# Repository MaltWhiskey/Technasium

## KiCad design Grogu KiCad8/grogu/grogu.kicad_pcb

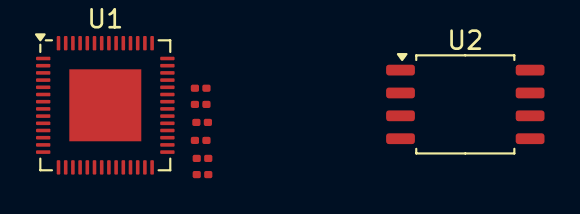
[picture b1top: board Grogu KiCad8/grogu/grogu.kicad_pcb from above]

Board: 2 copper layers, 8 parts (0 on the bottom side), 14 nets, no tracks yet.

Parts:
R1, R2, R3, R4, R5, R6: 0; R_0201_0603Metric
U1: ESP32-S3; QFN-56-1EP_7x7mm_P0.4mm_EP4x4mm
U2: W25Q128JVS; SOIC-8_5.23x5.23mm_P1.27mm

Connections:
/SPICLK: R4.2, U2.6 (CLK)
/SPICS: R3.2, U2.1 (~CS)
/SPID: R6.2, U2.5 (DI(IO0))
/SPIHD: R1.2, U2.7 (IO3)
/SPIQ: R5.2, U2.2 (DO(IO1))
/SPIWD: R2.2, U2.3 (IO2)
GND: U1.57 (GND), U2.8 (VCC)
unnamed: R4.1, U1.33 (SPICLK)
unnamed: R3.1, U1.32 (SPICS0)
unnamed: R6.1, U1.35 (SPID)
unnamed: R1.1, U1.30 (SPIHD)
unnamed: R5.1, U1.34 (SPIQ)
unnamed: R2.1, U1.31 (SPIWP)
VCC: U1.2 (VDD3P3), U1.3 (VDD3P3), U1.20 (VDD3P3_RTC), U1.29 (VDD_SPI), U1.46 (VDD3P3_CPU), U1.55 (VDDA), U1.56 (VDDA), U2.4 (GND)

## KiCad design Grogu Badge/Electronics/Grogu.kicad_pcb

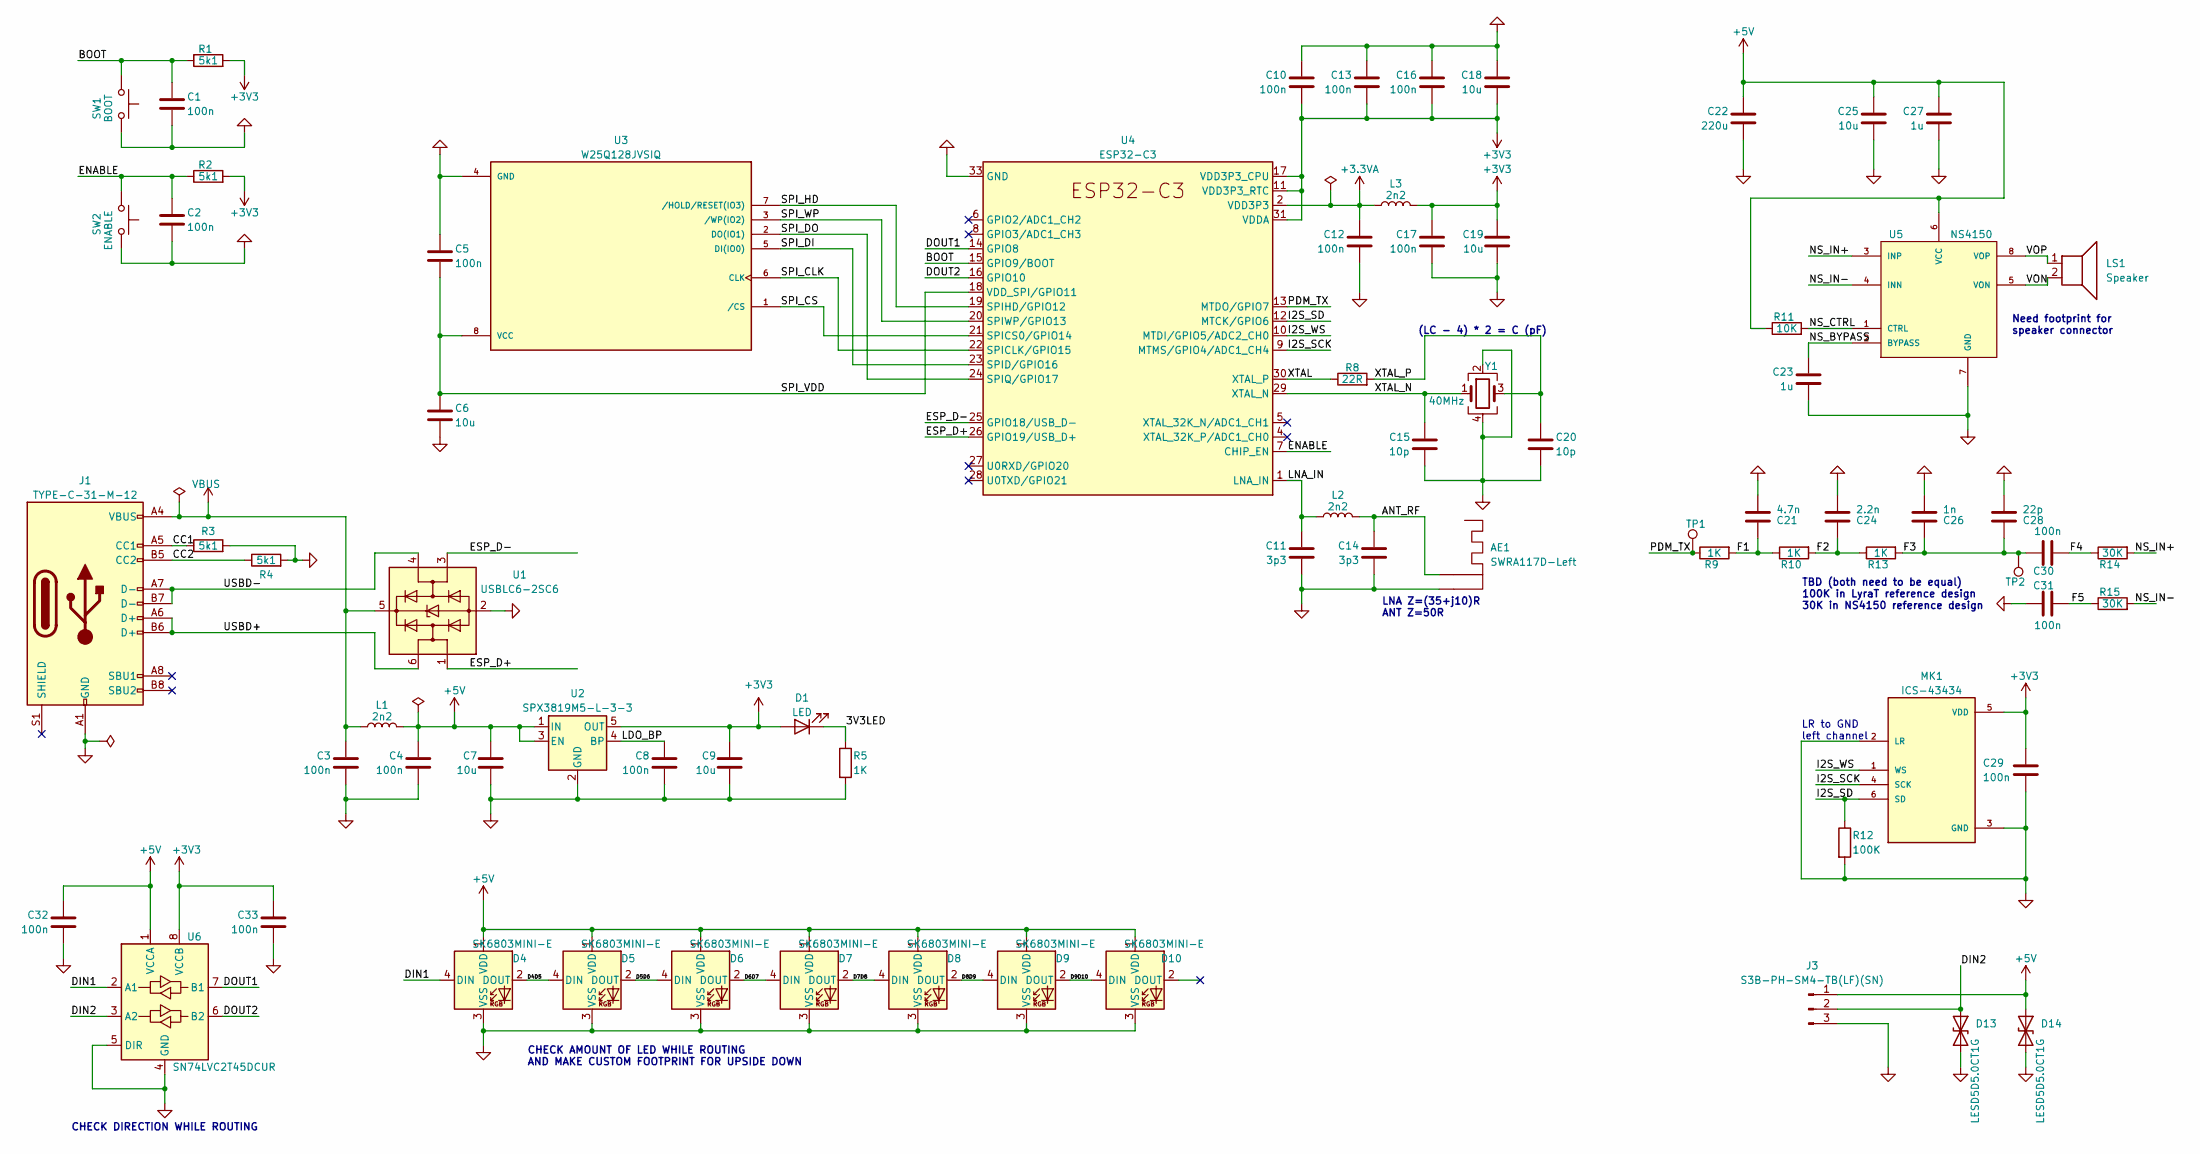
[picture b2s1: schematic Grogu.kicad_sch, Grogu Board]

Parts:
AE1: SWRA117D-Left; SWRA117D_2.4GHz_Left; PART# SWRA117D
C1, C2, C3, C4, C5, C8, C10, C12, C13, C16, C17, C29, C30, C31, C32, C33: 100n; C_0402_1005Metric; PART# C1525
C6, C7, C9, C18, C19, C25: 10u; C_0603_1608Metric; PART# C19702
C11, C14: 3p3; C_0402_1005Metric; PART# C1565
C15, C20: 10p; C_0402_1005Metric; PART# C32949
C21: 4.7n; C_0402_1005Metric; PART# C1538
C22: 220u; CP_Elec_6.3x7.7; PART# C340768
C23, C27: 1u; C_0805_2012Metric; PART# C15849
C24: 2.2n; C_0402_1005Metric; PART# C106861
C26: 1n; C_0402_1005Metric; PART# C106205
C28: 22p; C_0402_1005Metric; PART# C106203
D1: LED; LED_0805_2012Metric; PART# C84260
D4, D5, D6, D7, D8, D9, D10: SK6803MINI-E; LED_SK6812MINI_PLCC4_3.5x3.5mm_P1.75mm; PART# SK6803MINI-E
D13, D14: LESD5D5.0CT1G; D_SOD-523; PART# C383211
J1: TYPE-C-31-M-12; USB_C_Receptacle_HRO_TYPE-C-31-M-12; PART# C165948
J3: S3B-PH-SM4-TB(LF)(SN); JST_PH_S3B-PH-SM4-TB_1x03-1MP_P2.00mm_Horizontal; PART# C265101
L1, L2, L3: 2n2; L_0402_1005Metric; PART# C412264
LS1: Speaker; Speaker-0.5W-8Ohm
MK1: ICS-43434; PART# ICS-43434
R1, R2, R3, R4: 5k1; R_0402_1005Metric; PART# C105873
R5, R9, R10, R13: 1K; R_0402_1005Metric; PART# C25744
R8: 22R; R_0402_1005Metric; PART# C25092
R11: 10K; R_0402_1005Metric; PART# C25744
R12: 100K; R_0402_1005Metric; PART# C11702
R14, R15: 30K; R_0402_1005Metric; PART# C25744
SW1: BOOT; TS-1187A-B-A-B; PART# C318884
SW2: ENABLE; TS-1187A-B-A-B; PART# C318884
TP1, TP2: TestPoint; TestPoint_Pad_1.5x1.5mm
U1: USBLC6-2SC6; SOT-23-6; PART# C7519
U2: SPX3819M5-L-3-3; SOT-23-5; PART# C9055
U3: W25Q128JVSIQ; SOIC-8_5.275x5.275mm_P1.27mm; PART# C97521
U4: ESP32-C3; QFN-32-1EP_5x5mm_P0.5mm_EP3.45x3.45mm; PART# C2838500
U5: NS4150; MSOP-8_3x3mm_P0.65mm; PART# C189961
U6: SN74LVC2T45DCUR; VSSOP-8_2.4x2.1mm_P0.5mm; PART# C15741
Y1: 40MHz; Crystal_SMD_2520-4Pin_2.5x2.0mm; PART# C255973

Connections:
+3.3VA: C12.1, L3.1, U4.2 (VDD3P3), U4.3 (VDD3P3)
+3V3: C9.1, C10.1, C13.1, C16.1, C17.1, C18.1, C19.1, C29.1, C33.1, D1.2 (A), L3.2, MK1.5 (VDD), R1.2, R2.2, U2.5 (OUT), U4.11 (VDD3P3_RTC), U4.17 (VDD3P3_CPU), U4.31 (VDDA), U4.32 (VDDA), U6.8 (VCCB)
+5V: C4.1, C7.1, C22.2, C25.2, C27.2, C32.1, D4.1 (VDD), D5.1 (VDD), D6.1 (VDD), D7.1 (VDD), D8.1 (VDD), D9.1 (VDD), D10.1 (VDD), D14.1 (A1), J3.1, L1.2, R11.1, U2.1 (IN), U2.3 (EN), U5.6 (VCC), U6.1 (VCCA); also elsewhere on the board
/3V3LED: D1.1 (K), R5.1
/ANT_RF: AE1.2 (Feed), C14.1, L2.2
/BOOT: C1.1, R1.1, SW1.1, U4.15 (GPIO9/BOOT)
/CC1: J1.A5 (CC1), R3.1
/CC2: J1.B5 (CC2), R4.1
/D4D5: D4.2 (DOUT), D5.4 (DIN)
/D5D6: D5.2 (DOUT), D6.4 (DIN)
/D6D7: D6.2 (DOUT), D7.4 (DIN)
/D7D8: D7.2 (DOUT), D8.4 (DIN)
/D8D9: D8.2 (DOUT), D9.4 (DIN)
/D9D10: D9.2 (DOUT), D10.4 (DIN)
/DIN1: D4.4 (DIN), U6.2 (A1)
/DIN2: D13.1 (A1), J3.2, U6.3 (A2)
/DOUT1: U4.14 (GPIO8), U6.7 (B1)
/DOUT2: U4.16 (GPIO10), U6.6 (B2)
/ENABLE: C2.1, R2.1, SW2.1, U4.7 (CHIP_EN)
/ESP_D+: U1.1 (I/O1), U4.26 (GPIO19/USB_D+)
/ESP_D-: U1.3 (I/O2), U4.25 (GPIO18/USB_D-)
/F1: C21.2, R9.2, R10.1
/F2: C24.2, R10.2, R13.1
/F3: C26.2, C28.2, C30.2, R13.2, TP2.1
/F4: C30.1, R14.1
/F5: C31.1, R15.1
/I2S_SCK: MK1.4 (SCK), U4.9 (MTMS/GPIO4/ADC1_CH4)
/I2S_SD: MK1.6 (SD), R12.1, U4.12 (MTCK/GPIO6)
/I2S_WS: MK1.1 (WS), U4.10 (MTDI/GPIO5/ADC2_CH0)
/LDO_BP: C8.1, U2.4 (BP)
/LNA_IN: C11.1, L2.1, U4.1 (LNA_IN)
/NS_BYPASS: C23.2, U5.2 (BYPASS)
/NS_CTRL: R11.2, U5.1 (CTRL)
/NS_IN+: R14.2, U5.3 (INP)
/NS_IN-: R15.2, U5.4 (INN)
/PDM_TX: R9.1, TP1.1, U4.13 (MTDO/GPIO7)
/SPI_CLK: U3.6 (CLK), U4.22 (SPICLK/GPIO15)
/SPI_CS: U3.1 (/CS), U4.21 (SPICS0/GPIO14)
/SPI_DI: U3.5 (DI(IO0)), U4.23 (SPID/GPIO16)
/SPI_DO: U3.2 (DO(IO1)), U4.24 (SPIQ/GPIO17)
/SPI_HD: U3.7 (/HOLD/RESET(IO3)), U4.19 (SPIHD/GPIO12)
/SPI_VDD: C5.2, C6.1, U3.8 (VCC), U4.18 (VDD_SPI/GPIO11)
/SPI_WP: U3.3 (/WP(IO2)), U4.20 (SPIWP/GPIO13)
/USBD+: J1.A6 (D+), J1.B6 (D+), U1.6 (I/O1)
/USBD-: J1.A7 (D-), J1.B7 (D-), U1.4 (I/O2)
/VON: LS1.2, U5.5 (VON)
/VOP: LS1.1, U5.8 (VOP)
/XTAL: R8.1, U4.30 (XTAL_P)
/XTAL_N: C15.1, U4.29 (XTAL_N), Y1.1
/XTAL_P: C20.1, R8.2, Y1.3
GND: AE1.1 (Via), C1.2, C2.2, C3.2, C4.2, C5.1, C6.2, C7.2, C8.2, C9.2, C10.2, C11.2, C12.2, C13.2, C14.2, C15.2, C16.2, C17.2, C18.2, C19.2, C20.2, C21.1, C22.1, C23.1, C24.1, C25.1, C26.1, C27.1, C28.1, C29.2, C31.2, C32.2, C33.2, D4.3 (VSS), D5.3 (VSS), D6.3 (VSS), D7.3 (VSS), D8.3 (VSS), D9.3 (VSS), D10.3 (VSS), D13.2 (A2), D14.2 (A2), J1.A1 (GND), J1.A12 (GND), J1.B1 (GND), J1.B12 (GND), J3.3, MK1.2 (LR), MK1.3 (GND), R3.2, R4.2, R5.2, R12.2, SW1.2, SW2.2, U1.2 (GND), U2.2 (GND), U3.4 (GND), U4.33 (GND), U5.7 (GND), U6.4 (GND), U6.5 (DIR), Y1.2, Y1.4; also elsewhere on the board
VBUS: C3.1, J1.A4 (VBUS), J1.A9 (VBUS), J1.B4 (VBUS), J1.B9 (VBUS), L1.1, U1.5 (VBUS)

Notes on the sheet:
TBD (both need to be equal) 100K in LyraT reference design 30K in NS4150 reference design
CHECK DIRECTION WHILE ROUTING
(LC - 4) * 2 = C (pF)
CHECK AMOUNT OF LED WHILE ROUTING AND MAKE CUSTOM FOOTPRINT FOR UPSIDE DOWN
Need footprint for speaker connector
LNA Z=(35+j10)R ANT Z=50R
LR to GND left channel

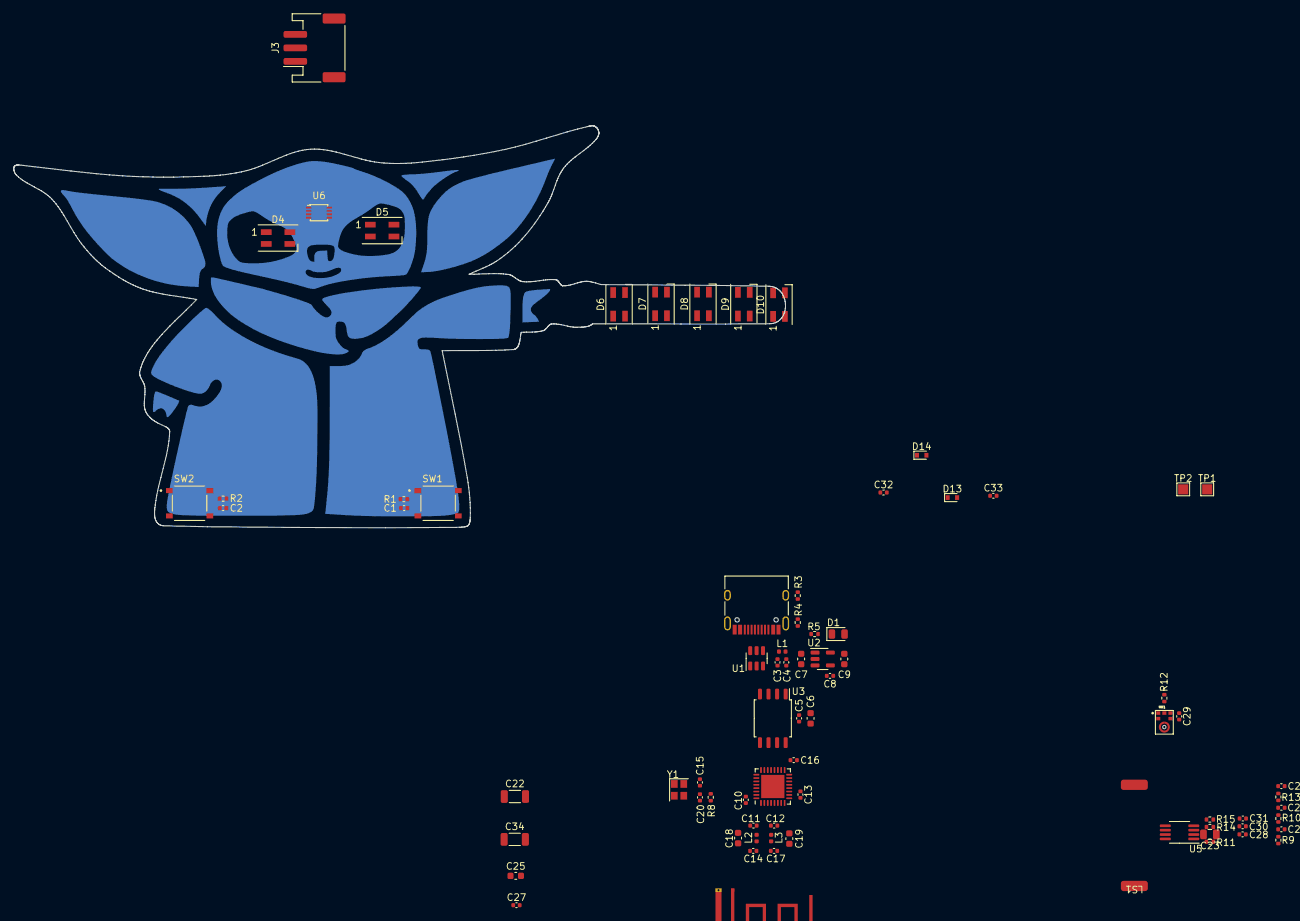
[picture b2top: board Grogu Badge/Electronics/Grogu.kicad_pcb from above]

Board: 2 copper layers, 114.4 x 59.6 mm, 76 parts (0 on the bottom side), 52 nets.

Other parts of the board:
C34: 100u; L_1206_3216Metric

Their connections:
+5V: C34.2; also elsewhere on the board
GND: C34.1; also elsewhere on the board

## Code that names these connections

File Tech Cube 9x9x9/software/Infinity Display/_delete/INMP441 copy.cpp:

/*
https://docs.espressif.com/projects/esp-idf/en/latest/esp32/api-reference/peripherals/i2s.html
https://docs.espressif.com/projects/esp-idf/en/v3.3.5/api-reference/peripherals/i2s.html
https://youtu.be/m-MPBjScNRk?si=TUU2Jdvn_8CnD2Ui
https://invensense.tdk.com/wp-content/uploads/2015/02/INMP441.pdf

INMP441 Microphone Features:
  1. Digital I2S interface with high precision 24-bit data
  2. High signal to noise ratio is 61 dBA
  3. High sensitivity - 26 dBFS
  4. Stable frequency response from 60 Hz to 15 kHz
  5. Low power consumption: low current consumption 1.4 mA
  6. High PSR: -75 dBFS

Interface definition:
  SCK: Serial data clock for I2S interface
  SD: Serial data output for I2S interface.
  WS: Serial data word select for I2S interface
  L/R: channel select:
    - When set low, the microphone outputs it's signal in the LEFT
        channel of the I2S frame.
    - When set high, the microphone outputs it's signals in the RIGHT
        channel of the I2S frame.

Hardware connection to ESP32:
  SD  >> GPIO21 >> GRAY (100k pulldown)
  SCK >> GPIO17 >> BROWN
  WS  >> GPIO16 >> WHITE
  L/R >> GND    >> PURPLE
  GND >> GND    >> BLACK
  VDD >> 3V3    >> RED

NOTE: Although the INMP441 is 24 bits, it needs 64 clock cycles for every
stereo data word. Therefore the I2S interface needs to use 32 bits per sample.
After 24 bits are transmitted, the SD line is tri-stated, it should be pulled
down with 100k to discharge the line.
*/

#include <Arduino.h>
#include <driver/i2s.h>

#define I2S_SD 21
#define I2S_SCK 17
#define I2S_WS 16
#define I2S_PORT I2S_NUM_0

namespace I2S_MIC {

void begin(uint32_t frequency) {
  const i2s_config_t i2s_config = {
      .mode = i2s_mode_t(I2S_MODE_MASTER | I2S_MODE_RX),
      .sample_rate = frequency,
      .bits_per_sample = I2S_BITS_PER_SAMPLE_32BIT,
      .channel_format = I2S_CHANNEL_FMT_ONLY_RIGHT,
      .communication_format = i2s_comm_format_t(I2S_COMM_FORMAT_STAND_I2S),
      .intr_alloc_flags = 0,
      .dma_buf_count = 8,
      .dma_buf_len = 1024,
      .use_apll = true,
      .tx_desc_auto_clear = false,
      .fixed_mclk = 0};

  const i2s_pin_config_t pin_config = {.bck_io_num = I2S_SCK,
                                       .ws_io_num = I2S_WS,
                                       .data_out_num = I2S_PIN_NO_CHANGE,
                                       .data_in_num = I2S_SD};
  if (esp_err_t err =
          i2s_driver_install(I2S_PORT, &i2s_config, 0, NULL) != ESP_OK)
    Serial.printf("Failed installing driver: %d\n", err);
  else if (err = i2s_set_pin(I2S_PORT, &pin_config) != ESP_OK)
    Serial.printf("Failed setting pin: %d\n", err);
  else if (err = i2s_start(I2S_NUM_0) != ESP_OK)
    Serial.printf("Failed starting I2S: %d\n", err);
  else
    Serial.println("I2S driver installed");
}

uint16_t loop(int16_t *sample_data, const uint16_t samples) {
  // Memory for audio samples (24 bits per sample stored in signed 32 bit)
  int32_t buffer[100];
  uint16_t bytes_remaining = samples << 1;
  uint16_t samples_read = 0;
  while (bytes_remaining > 0) {
    size_t bytes_read = 0;
    uint16_t bytes_to_read = min(bytes_remaining, (uint16_t)sizeof(buffer));
    if (esp_err_t err = i2s_read(I2S_PORT, buffer, bytes_to_read, &bytes_read,
                                 100) != ESP_OK) {
      Serial.printf("ERR %d\n", err);
      return 0;
    }
    bytes_remaining -= bytes_read;
    for (uint16_t i = 0; i < bytes_read >> 1; i++) {
      sample_data[samples_read++] = buffer[i] >> 16;
    }
  }
  return samples_read;
}
}  // namespace I2S_MIC

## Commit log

2023-03-09 I hate DS_Store
2023-03-09 Easy sample
2023-03-09 easier example
2023-04-14 src control
2023-04-14 test
2023-04-14 docs
2023-04-14 pics
2023-05-08 prepare
2023-05-16 Clean up workspace
2023-05-17 new version
2023-05-23 Minor fixes
2023-05-30 movie
2023-06-13 Spellingsfout
2023-06-14 Hacked white frame for testing
2023-06-15 New box
2023-08-23 Feedback van ws verwerkt
2023-08-28 Update env
2023-08-29 New example
2023-08-29 Rename Where is my Jet?.svg to Where is my Jet.svg
    Windows doesnt like some characters
2023-08-29 animation update
2023-08-31 fresh init
2023-08-31 New fusion version
2023-09-22 add Webpage
2023-09-26 anim
2023-09-26 merge
2023-09-29 update led cube webpage
2023-10-11 faster
2023-10-11 better
2023-10-11 stronger
2023-10-24 done
2023-10-27 ini windows fix
2023-11-03 opsolete
2023-11-06 Big cube
2023-11-06 added webserver
2023-11-11 Webserver added
2023-11-30 working on i2s
2023-12-03 kill node.js use python instead
2023-12-04 sych
2023-12-04 synch
2023-12-06 test fft
2023-12-27 Tweaks
2023-12-27 demo mode lines
2023-12-30 cube anim
2023-12-30 buggy source control commit
2023-12-30 buggy
2023-12-30 fhsjklfjkdsfh
2023-12-30 hjjgjjg
2024-01-17 css mooi
2024-01-17 catch exception
2024-02-05 yield to webserver task
2024-02-05 rem def
2024-02-12 sadkljflksdjflkfj
2024-02-16 bug in esp32 wificlient
2024-02-17 IDF change
2024-02-18 kghkgk
2024-02-18 joystick control since accel needs https
2024-02-19 factory reset added
2024-03-17 new mac
2024-04-03 grogu
2024-04-21 motor
2024-04-22 Motor on Interrupt
2024-04-26 other motor
2024-04-27 update stepperdriver
2024-05-13 fix filenames advanced exemple
2024-06-07 Prep 2024 WS
2024-06-07 motor speed
2024-06-07 more controls
2024-06-11 temp file weg
2024-06-11 programma 2024
2024-06-11 prog fll
2024-06-12 leesbaarheid
2024-06-17 new scroller
2024-06-21 charlie
2024-06-26 Nice Blink
2024-06-26 gdrgfdhe3gy
2024-06-26 trrtaert
2024-06-26 timing
2024-07-05 add the new webpage
2024-07-10 Refactoring
2024-07-10 refactor
2024-10-24 Added Train
2024-10-24 Work in progress
2024-10-24 not needed
2024-10-24 fx ws
2025-03-14 make the train go into deepsleep after a workday
